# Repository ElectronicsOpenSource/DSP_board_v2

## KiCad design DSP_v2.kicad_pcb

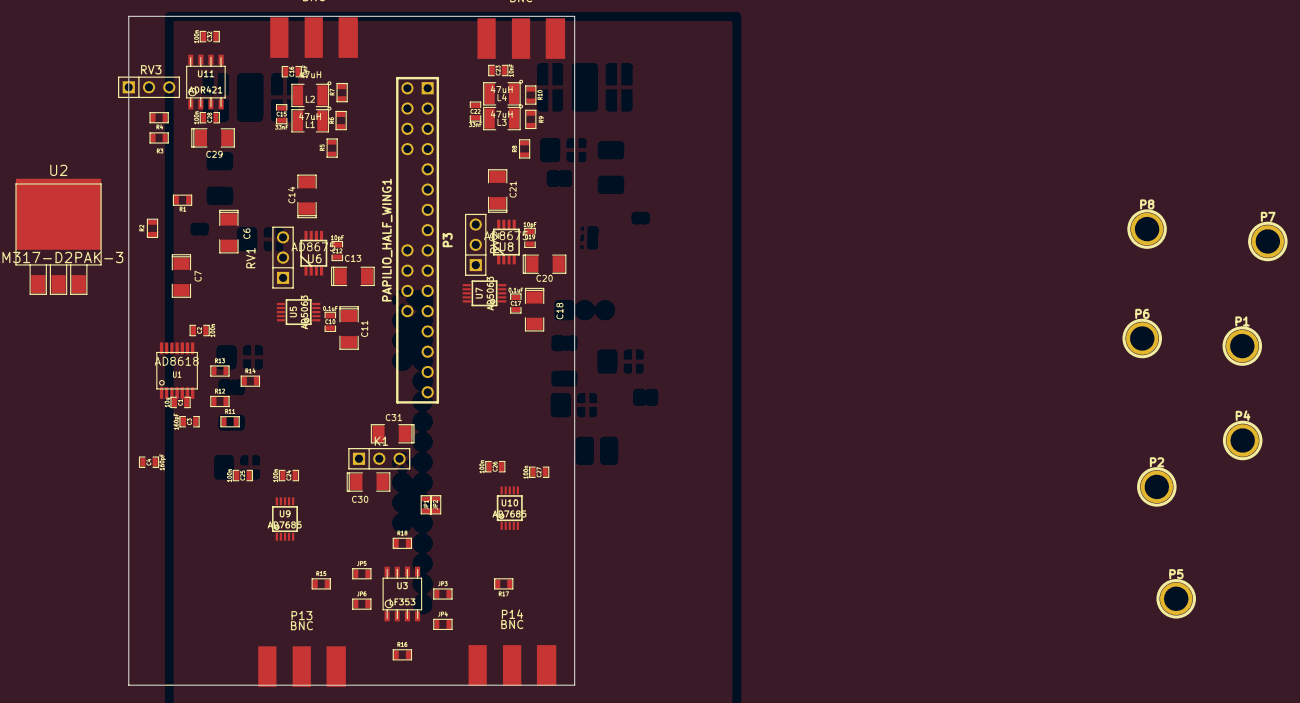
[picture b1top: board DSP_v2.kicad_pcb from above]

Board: 2 copper layers, 55.9 x 83.8 mm, 83 parts (0 on the bottom side), 54 nets, no tracks yet.

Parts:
C1: 10u; SM0603_Capa
C2, C24, C25, C26, C27, C28, C32: 100n; SM0603_Capa
C3, C4: 160pF; SM0603_Capa
C6: 100n; SM1206POL
C7: 1u; SM1206POL
C10, C17: 0.1uF; SM0603_Capa
C11, C18: 10uF; SM1206POL
C12, C19: 10pF; SM0603_Capa
C13, C14, C20, C21: 0.1uF; SM1206POL
C15, C22: 33nF; SM0603_Capa
C16, C23: 10nF; SM0603_Capa
C29, C30, C31: 10u; SM1206POL
JP1, JP2, JP3, JP4, JP5, JP6: JUMPER; SM0603
K1: CONN_3; PIN_ARRAY_3X1
L1, L2, L3, L4: 47uH; SM1210
P1, P2, P4, P5, P6, P7, P8: CONN_1; 1pin
P3: PAPILIO_HALF_WING1; Papilio_Half_Wing_1
P11, P12, P13, P14: BNC; sma-side
R1: 768R; SM0603
R2: 220R; SM0603
R3: 470k; SM0603
R4: 15k; SM0603
R5, R8: short; SM0603
R6, R7, R9, R10: 50; SM0603
R11, R12, R13, R16, R18: 1k; SM0603
R14, R15, R17: 4k; SM0603
RV1, RV2: 100K; PIN_ARRAY_3X1
RV3: 10k; PIN_ARRAY_3X1
U1: AD8618; tssop-14
U2: LM317-D2PAK-3; DPAK3
U3: LF353; so-8
U5, U7: AD5063; MSOP10-0.5
U6, U8: AD8675; MSOP_8
U9, U10: AD7685; MSOP10-0.5
U11: ADR421; so-8

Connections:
2VREF: C2.1, JP4.1, JP6.1, P6.1, R13.2, R14.1
5VREF: JP2.2, JP3.1, JP5.1, P7.1, U1.13, U1.14, U9.1, U10.1
+2.5V: JP1.2, P1.1, U1.1, U1.2, U5.3, U7.3
+3.3V: C24.1, C26.1, P3.18, P3.21, U9.9, U9.10, U10.9, U10.10
+5P: C7.1, P2.1, R2.1, U1.4, U2.2
-VAA: C13.1, C20.1, C31.1, K1.3, U3.4, U6.4, U8.4
/ADC1/CNV: P3.11, U9.6
/ADC1/SCK: P3.9, U9.8
/ADC1/SDO: P3.10, U9.7
/ADC2/CNV: P3.16, U10.6
/ADC2/SCK: P3.14, U10.8
/ADC2/SDO: P3.15, U10.7
/DAC1/CS: P3.1, U7.9
/DAC1/DATA: P3.3, U7.1
/DAC1/SCLK: P3.2, U7.10
/DAC2/CS: P3.6, U5.9
/DAC2/DATA: P3.8, U5.1
/DAC2/SCLK: P3.7, U5.10
ADVDD: C25.2, C27.2, JP1.1, JP2.1, U9.2, U10.2
AGND: C1.2, C2.2, C6.2, C7.2, C10.2, C11.2, C13.2, C14.2, C15.2, C16.2, C17.2, C18.2, C20.2, C21.2, C22.2, C23.2, C24.2, C25.1, C26.2, C27.1, C28.2, C29.2, C30.2, C31.2, C32.2, K1.2, P3.17, P3.20, P8.1, P11.2, P12.2, P13.2, P14.2, R1.2, R4.2, R7.2, R10.2, R11.2, R14.2, U1.11, U5.7, U5.8, U7.7, U7.8, U9.4, U9.5, U10.4, U10.5, U11.4
unnamed: C1.1, R13.1, U1.6, U1.7, U1.10
unnamed: R12.2, U1.8, U1.12
unnamed: R4.1, RV3.1
unnamed: R3.2, RV3.2
unnamed: R3.1, U11.5
unnamed: R11.1, R12.1, U1.9
unnamed: R1.1, R2.2, U2.1
unnamed: C32.1, RV3.3, U1.3, U1.5, U11.6
unnamed: L1.1, R6.2
unnamed: C15.1, L1.2, L2.1
unnamed: C12.1, R5.1, R6.1, U5.6, U6.6
unnamed: C16.1, L2.2, P11.1, R5.2, R7.1
unnamed: C12.2, U5.4, U6.3
unnamed: RV1.1, U6.1
unnamed: RV1.3, U6.8
unnamed: U5.5, U6.2
unnamed: L3.1, R9.2
unnamed: C22.1, L3.2, L4.1
unnamed: C19.1, R8.1, R9.1, U7.6, U8.6
unnamed: C23.1, L4.2, P12.1, R8.2, R10.1
unnamed: C19.2, U7.4, U8.3
unnamed: RV2.1, U8.1
unnamed: RV2.3, U8.8
unnamed: U7.5, U8.2
unnamed: JP5.2, JP6.2, U3.5
unnamed: P14.1, R17.1
unnamed: C4.2, R17.2, R18.1, U3.6
unnamed: C4.1, R18.2, U3.7, U10.3
unnamed: JP3.2, JP4.2, U3.3
unnamed: P13.1, R15.1
unnamed: C3.2, R15.2, R16.1, U3.2
unnamed: C3.1, R16.2, U3.1, U9.3
VAA: C6.1, C14.1, C21.1, C28.1, C29.1, C30.1, K1.1, RV1.2, RV2.2, U2.3, U3.8, U6.7, U8.7, U11.2
VDD: C10.1, C11.1, C17.1, C18.1, U5.2, U7.2

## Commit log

2015-02-25 Current version of the board including OSPESA libraries and footprints
